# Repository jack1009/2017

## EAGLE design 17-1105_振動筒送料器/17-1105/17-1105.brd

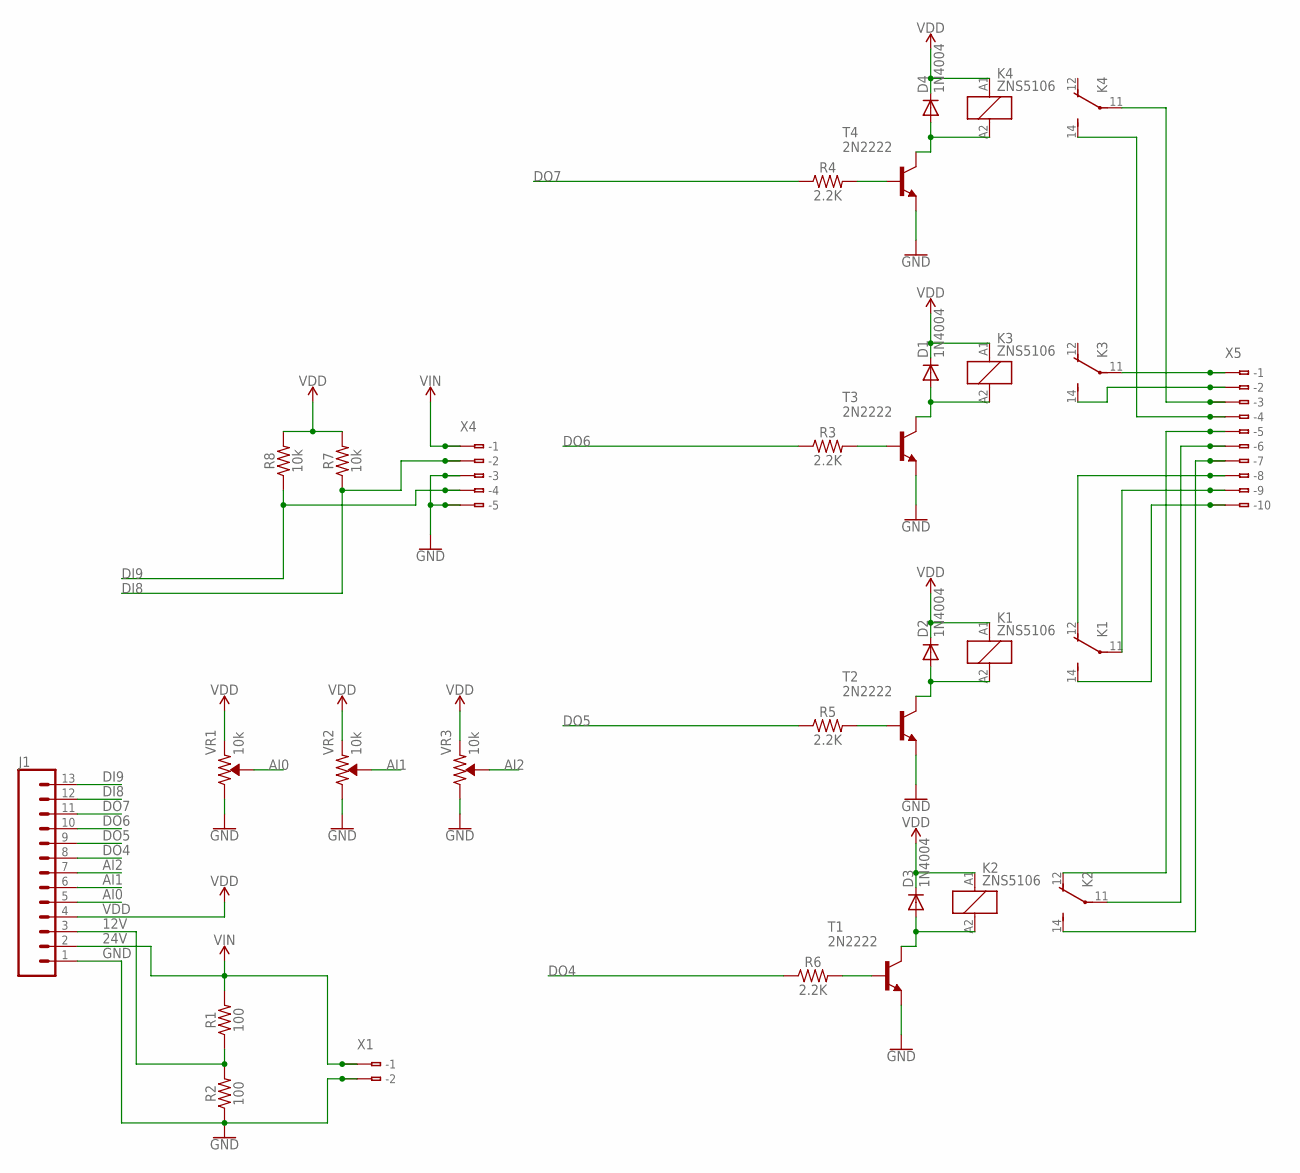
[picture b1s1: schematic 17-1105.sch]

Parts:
D1, D2, D3, D4: 1N4004; DO41-10
J1: CONN_13; 1X13
K1, K2, K3, K4: ZNS5106; ZN5
R1, R2: 100; AXIAL-0.3
R3, R4, R5, R6: 2.2K; AXIAL-0.3
R7, R8: 10k; AXIAL-0.3
T1, T2, T3, T4: 2N2222; TO92-EBC-OVAL
VR1, VR2, VR3: 10k; TRIMPOT-PTH-3386U
X1: 233-102
X4: 233-105
X5: 233-110

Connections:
12V: J1.3, R1.P$1 (1), R2.P$2 (2)
24V: J1.2, R1.P$2 (2), X1.A1 (-1), X1.B1 (B-1), X4.A1 (-1), X4.B1 (B-1)
AI0: J1.5, VR1.2 (WIPER)
AI1: J1.6, VR2.2 (WIPER)
AI2: J1.7, VR3.2 (WIPER)
DI8: J1.12, R7.P$1 (1), X4.A2 (-2), X4.B2 (B-2)
DI9: J1.13, R8.P$1 (1), X4.A4 (-4), X4.B4 (B-4)
DO4: J1.8, R6.P$1 (1)
DO5: J1.9, R5.P$1 (1)
DO6: J1.10, R3.P$1 (1)
DO7: J1.11, R4.P$1 (1)
GND: J1.1, R2.P$1 (1), T1.E, T2.E, T3.E, T4.E, VR1.3 (CW), VR2.3 (CW), VR3.3 (CW), X1.A2 (-2), X1.B2 (B-2), X4.A3 (-3), X4.A5 (-5), X4.B3 (B-3), X4.B5 (B-5)
unnamed: D1.A, K3.A2 (2), T3.C
unnamed: D4.A, K4.A2 (2), T4.C
unnamed: K2.12 (O), X5.A5 (-5), X5.B5 (B-5)
unnamed: R5.P$2 (2), T2.B
unnamed: D3.A, K2.A2 (2), T1.C
unnamed: D2.A, K1.A2 (2), T2.C
unnamed: R6.P$2 (2), T1.B
unnamed: K2.14 (S), X5.A7 (-7), X5.B7 (B-7)
unnamed: K2.11, X5.A6 (-6), X5.B6 (B-6)
unnamed: K1.12 (O), X5.A8 (-8), X5.B8 (B-8)
unnamed: K4.11, X5.A3 (-3), X5.B3 (B-3)
unnamed: K3.14 (S), X5.A2 (-2), X5.B2 (B-2)
unnamed: K3.11, X5.A1 (-1), X5.B1 (B-1)
unnamed: R4.P$2 (2), T4.B
unnamed: K1.11, X5.A9 (-9), X5.B9 (B-9)
unnamed: K1.14 (S), X5.A10 (-10), X5.B10 (B-10)
unnamed: R3.P$2 (2), T3.B
unnamed: K4.14 (S), X5.A4 (-4), X5.B4 (B-4)
VDD: D1.C, D2.C, D3.C, D4.C, J1.4, K1.A1 (1), K2.A1 (1), K3.A1 (1), K4.A1 (1), R7.P$2 (2), R8.P$2 (2), VR1.1 (CCW), VR2.1 (CCW), VR3.1 (CCW)

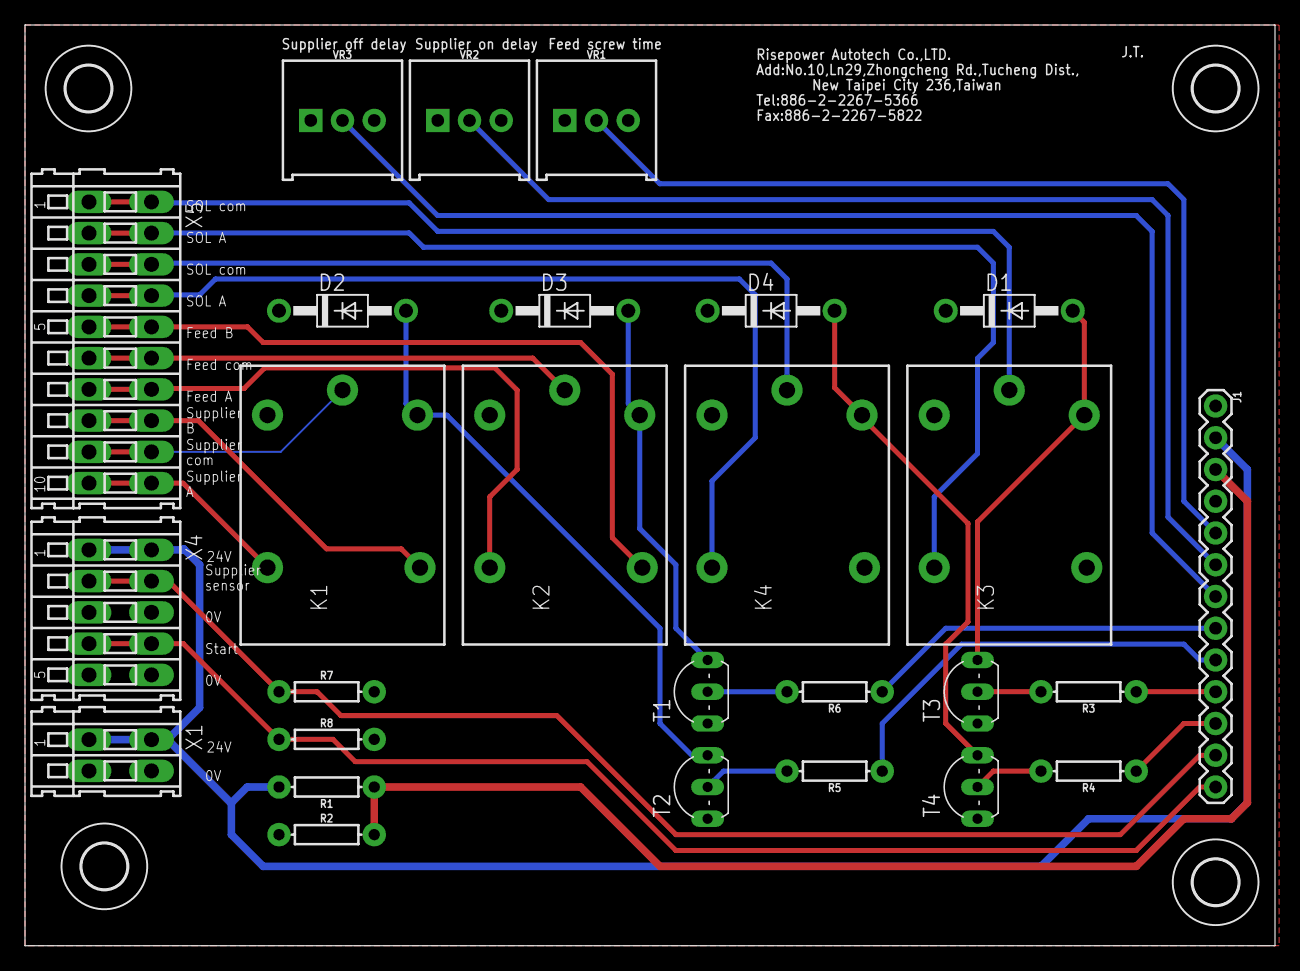
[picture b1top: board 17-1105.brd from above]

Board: 2 copper layers, 100.0 x 73.7 mm, 31 parts (0 on the bottom side), 31 nets.

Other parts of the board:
U$1, U$2, U$3, U$4: 3,6

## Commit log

2021-12-22 NewFiles
    2017年存檔

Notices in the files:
parts and their libraries:
SparkFun-Resistors: Licensing: Creative Commons ShareAlike 4.0 International - https://creativecommons.org/licenses/by-sa/4.0
